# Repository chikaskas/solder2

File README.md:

# solder2
**Submission** for https://solder.hackclub.com

**Description**: My PCB is very simple. There is a button that turns the LED on and a button that turns the LED off. I used a capacitor to store the charge provided by the battery through the push button and used 2 NPN transistors to amplify the current (so the capacitor doesn't discharge quickly).

**Bill**:
1x red LED, 
4x 4.7k resistor, 
2x NPN transistor, 
1x capacitor, 
2x push button, 
2x battery cell, 

**Pictures**:

Simulation:

Schematic:

PCB:

3D preview:

Made by @chikaskas

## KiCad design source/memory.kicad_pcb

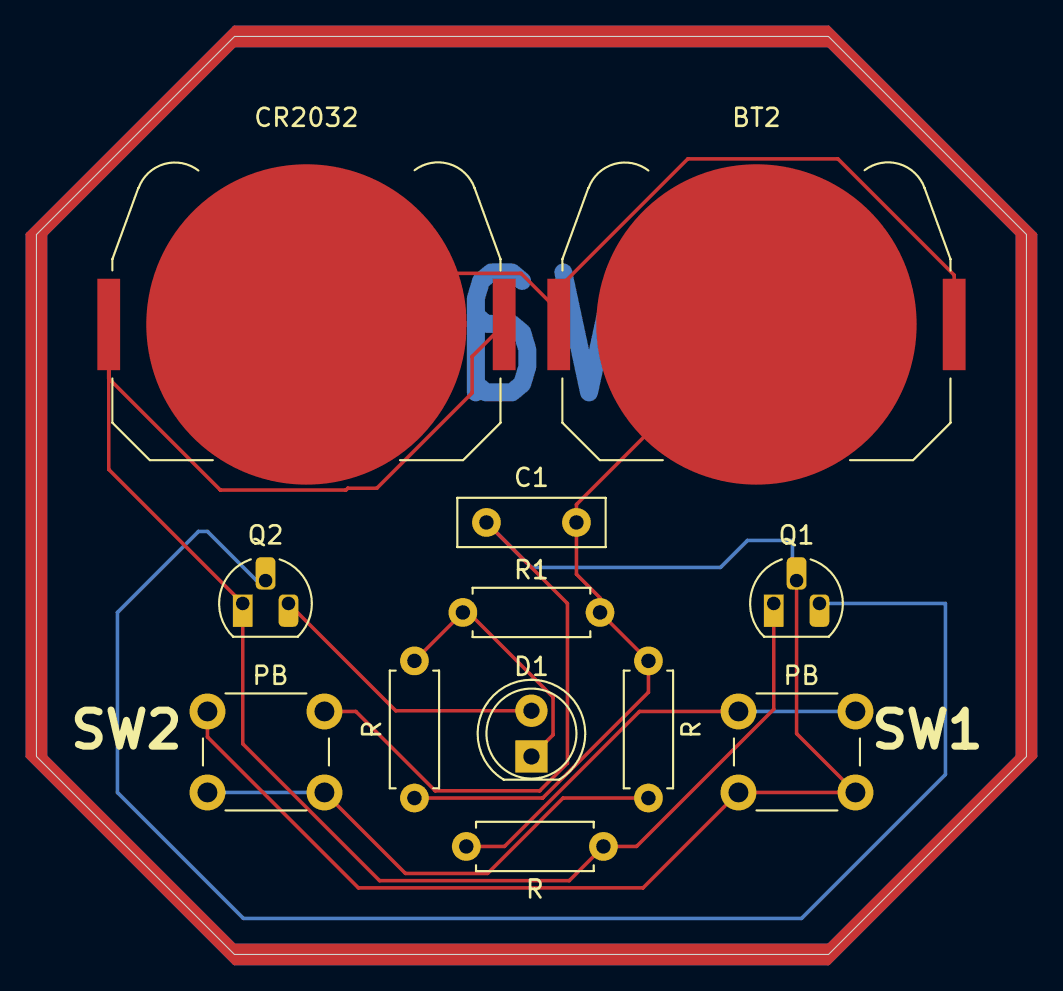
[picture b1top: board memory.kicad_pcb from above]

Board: 2 copper layers, 55.0 x 51.0 mm, 12 parts (0 on the bottom side), 9 nets.

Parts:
BT1, BT2: Battery_Cell; BatteryHolder_Keystone_3034_1x20mm
C1: C; C_Disc_D8.0mm_W2.5mm_P5.00mm
D1: LED; LED_D5.0mm
Q1, Q2: NPN; TO-92L_HandSolder
R1, R2, R3, R4: R; R_Axial_DIN0207_L6.3mm_D2.5mm_P7.62mm_Horizontal
SW1, SW2: SW_Push; SW_PUSH_6mm

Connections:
unnamed: BT1.1 (+), Q1.1 (C), Q2.1 (C), R3.2
unnamed: BT1.2 (-), BT2.1 (+)
unnamed: BT2.2 (-), C1.2, R1.2, R2.2, R4.2
unnamed: D1.2 (A), Q2.3 (E)
unnamed: D1.1 (K), R1.1, R2.1
unnamed: C1.1, Q1.2 (B), SW1.2, SW2.1
unnamed: Q1.3 (E), Q2.2 (B)
unnamed: R3.1, SW1.1
unnamed: R4.1, SW2.2

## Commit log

2025-06-28 Add KiCAD files
